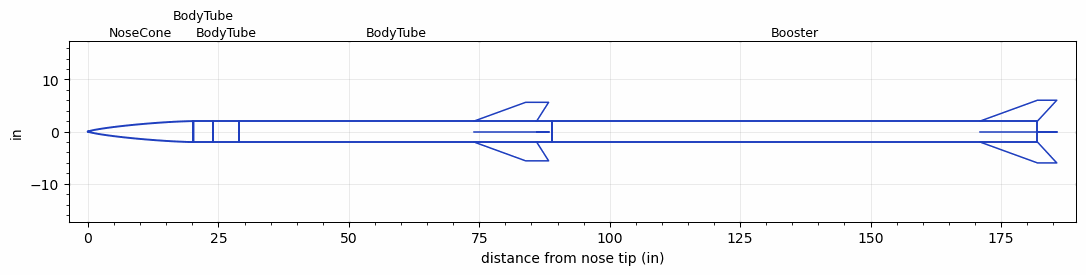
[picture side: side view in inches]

<RASAeroDocument>
 <FileVersion>2</FileVersion>
 <RocketDesign>
  <NoseCone>
   <Length>20.21</Length>
   <Diameter>4.02</Diameter>
   <Shape>Von Karman Ogive</Shape>
   <Location>0</Location>
  </NoseCone>
  <BodyTube>
   <Length>3.79</Length>
   <Diameter>4.02</Diameter>
   <Location>20.21</Location>
  </BodyTube>
  <BodyTube>
   <Length>5</Length>
   <Diameter>4.02</Diameter>
   <Location>24</Location>
  </BodyTube>
  <BodyTube>
   <Length>60</Length>
   <Diameter>4.02</Diameter>
   <Location>29</Location>
   <Fin>
    <Count>4</Count>
    <Chord>12</Chord>
    <Span>3.6</Span>
    <SweepDistance>9.891</SweepDistance>
    <TipChord>4.4</TipChord>
    <Thickness>0.28</Thickness>
    <LERadius>0.11</LERadius>
    <Location>15</Location>
    <AirfoilSection>Hexagonal</AirfoilSection>
    <FX1>1</FX1>
    <FX3>1</FX3>
   </Fin>
  </BodyTube>
  <Booster>
   <Length>93</Length>
   <Diameter>4.02</Diameter>
   <InsideDiameter>4.02</InsideDiameter>
   <Location>89</Location>
   <ShoulderLength>0</ShoulderLength>
   <Fin>
    <Count>4</Count>
    <Chord>11</Chord>
    <Span>4</Span>
    <SweepDistance>11</SweepDistance>
    <TipChord>3.7</TipChord>
    <Thickness>0.3</Thickness>
    <LERadius>0.11</LERadius>
    <Location>11</Location>
    <AirfoilSection>Hexagonal</AirfoilSection>
    <FX1>1</FX1>
    <FX3>1</FX3>
   </Fin>
  </Booster>
  <Surface>Smooth Paint</Surface>
  <ModifiedBarrowman>True</ModifiedBarrowman>
  <Turbulence>True</Turbulence>
  <UseBooster1>False</UseBooster1>
  <UseBooster2>False</UseBooster2>
 </RocketDesign>
 <LaunchSite>
  <Altitude>2000</Altitude>
  <Pressure>0</Pressure>
  <RodAngle>3</RodAngle>
  <RodLength>20</RodLength>
  <Temperature>70</Temperature>
  <WindSpeed>10</WindSpeed>
 </LaunchSite>
 <Recovery>
  <Altitude1>1000</Altitude1>
  <Altitude2>1000</Altitude2>
  <DeviceType1>None</DeviceType1>
  <DeviceType2>None</DeviceType2>
  <Event1>False</Event1>
  <Event2>False</Event2>
  <Size1>1</Size1>
  <Size2>1</Size2>
  <EventType1>None</EventType1>
  <EventType2>None</EventType2>
  <CD1>1.33</CD1>
  <CD2>1.33</CD2>
 </Recovery>
 <SimulationList>
  <Simulation>
   <SustainerEngine>M685W-PS  (AT)</SustainerEngine>
   <SustainerLaunchWt>33.8</SustainerLaunchWt>
   <SustainerNozzleDiameter>2.557</SustainerNozzleDiameter>
   <SustainerCG>55.88</SustainerCG>
   <SustainerIgnitionDelay>8</SustainerIgnitionDelay>
   <Booster1Engine>O5500X  (AT)</Booster1Engine>
   <Booster1LaunchWt>84.4</Booster1LaunchWt>
   <Booster1SeparationDelay>0</Booster1SeparationDelay>
   <Booster1IgnitionDelay>0</Booster1IgnitionDelay>
   <Booster1CG>109</Booster1CG>
   <Booster1NozzleDiameter>3.6</Booster1NozzleDiameter>
   <IncludeBooster1>True</IncludeBooster1>
   <Booster2Delay>0</Booster2Delay>
   <IncludeBooster2>False</IncludeBooster2>
   <TimetoApogee>81.52815</TimetoApogee>
   <MaxAltitude>96755.49</MaxAltitude>
   <MaxVelocity>2438.997</MaxVelocity>
  </Simulation>
 </SimulationList>
</RASAeroDocument>
